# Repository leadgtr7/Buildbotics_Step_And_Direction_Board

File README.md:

Buildbotics Step and Direction Breakout and Level Shifter
======

### Intro
This is a step and direction breakout board and level shifter for the awesome Buildbotics CNC controller (https://buildbotics.com/ and https://github.com/buildbotics).

This board has been tested with the CL57Y closed loop stepper driver (https://www.omc-stepperonline.com/closed-loop-stepper-driver/y-series-closed-loop-stepper-driver-0-7-0a-24-50vdc-for-nema-17-23-24-stepper-motor.html).

I suspect that it will work with most drivers that have a minimum pulse width of 2.5uS even though the buildbotics control has a pulse width of 2 uS it just seems to work.

This board involves some small surface mount components (SOIC-8) so soldering skills are a must!

### You will need the following parts for the board

| Qty	| P/N	| Digikey Link |
| ---- | ---- | ---- | 
|4x	|SN75451BDR	|https://www.digikey.com/product-detail/en/texas-instruments/SN75451BDR/296-14960-1-ND/562591|
|12x	|Generic Header Pins 2.54mm spacing	|https://www.amazon.com/MCIGICM-Header-2-45mm-Arduino-Connector/dp/B07PKKY8BX/ref=sr_1_4?keywords=header+pins&qid=1579894443&sr=8-4|
|2x	|PCB-MB-01|https://www.digikey.com/product-detail/en/essentra-components/PCB-MB-01/RPC1760-ND/393158|
|4x |3 pin plugable terminal blocks 3.81mm spacing |https://www.amazon.com/gp/product/B07SVNGBZ7/ref=ppx_yo_dt_b_search_asin_title?ie=UTF8&psc=1|
|4x |0805 0.1uF Cap|https://www.digikey.com/product-detail/en/stackpole-electronics-inc/CML0805Y5V104ZT50V/738-CML0805Y5V104ZT50VCT-ND/10660252|

### Buildbotics PCB Modifications
You will need to solder in headers to the bbctrl board to make step and direction available as well as a 2 pin header with 5v and Ground. This will vary based on the version of your control board. You can find the schematics for the differnt revs here (https://github.com/buildbotics/bbctrl-pcb/tree/master/doc). For my controller (rev 8) you can see below for the locations.

You will also need to make a harness to connect the 10 pins on the bbctrl to the step and direction board. If you aren't comfortable crimping your own harness you could use something like this (https://www.amazon.com/EDGELEC-Breadboard-Optional-Assorted-Multicolored/dp/B07GCY6CH7/ref=sr_1_3?keywords=header%2Bwire&qid=1579895256&sr=8-3&th=1) for your harness.

### PCB Assembly
The image below shows the location of all the headers and how to solder the ICs to the board. Each of the 3 pin connectors provides the step and direction output and the 4 sets of 2 pins are wired to the buildbotics pcb header you need to install. Remeber that as you plug in the cable on the back that they will be reversed on the front so pay attention to that.

note the direction of pin 1 of the IC's

### New Back Panel
The back of the buildbotics controller can be modified to accommodate the new board using the any of the files in the back panel folder. I use fusion 360 so i have included a fusion file with all of my tool paths and the like. You could also use the step file. 

I Used 1/16th in aluminum sheet to recreate the back piece (https://www.amazon.com/dp/B00HRHBB20/?coliid=IMIUESINE7ACL&colid=2XXWKYU69Q3UG&psc=1&ref_=lv_ov_lig_dp_it).

back panel

I think that about covers it. Thanks to Joe and Doug from buildbotics for an awesome product and helping me out in modifying the controller to suit my needs.

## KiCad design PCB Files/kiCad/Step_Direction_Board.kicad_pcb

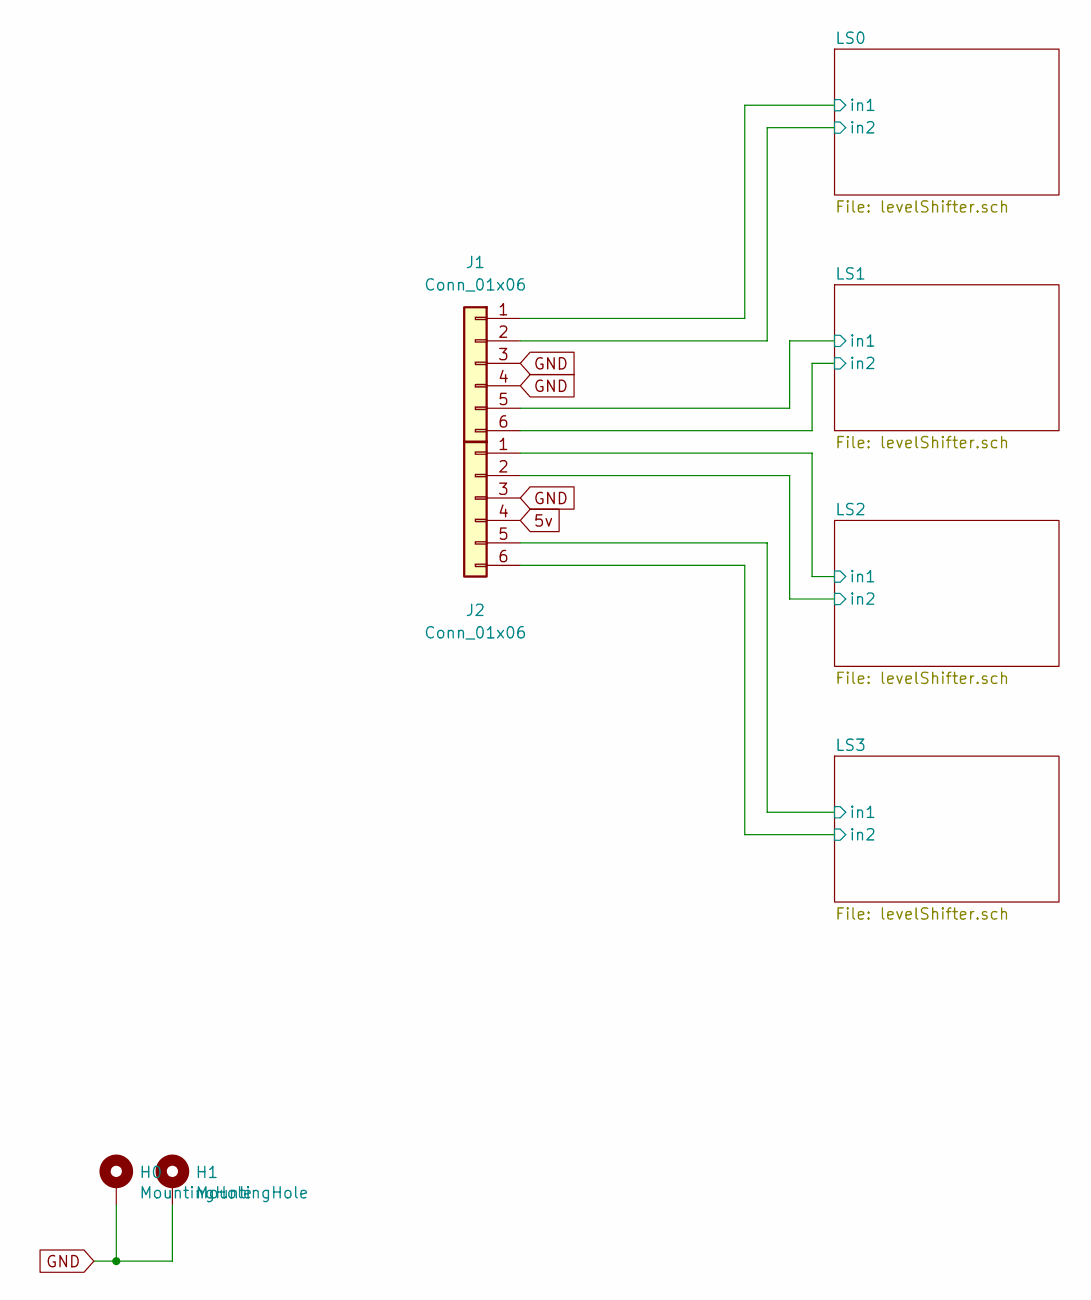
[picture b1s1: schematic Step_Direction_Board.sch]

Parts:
H0, H1: MountingHole; MountingHole_3.2mm_M3_ISO7380_Pad
J1, J2: Conn_01x06; PinHeader_1x06_P2.54mm_Horizontal

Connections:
5v: J2.4; also elsewhere on the board
/LS0/in1: J1.1; also elsewhere on the board
/LS0/in2: J1.2; also elsewhere on the board
/LS1/in1: J1.5; also elsewhere on the board
/LS1/in2: J1.6; also elsewhere on the board
/LS2/in1: J2.1; also elsewhere on the board
/LS2/in2: J2.2; also elsewhere on the board
/LS3/in1: J2.5; also elsewhere on the board
/LS3/in2: J2.6; also elsewhere on the board
GND: H0.1, H1.1, J1.3, J1.4, J2.3; also elsewhere on the board

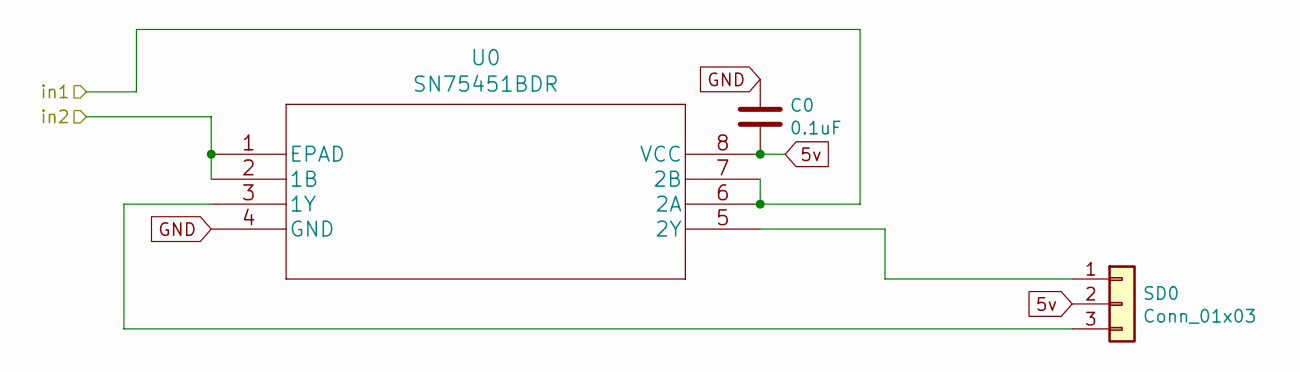
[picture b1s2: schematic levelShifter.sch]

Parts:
C0: 0.1uF; C_0805_2012Metric_Pad1.15x1.40mm_HandSolder
SD0: Conn_01x03; PhoenixContact_MC_1,5_3-G-3.81_1x03_P3.81mm_Horizontal
U0: SN75451BDR

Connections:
5v: C0.2, SD0.2, U0.8 (VCC); also elsewhere on the board
/LS0/in1: U0.6 (2A), U0.7 (2B); also elsewhere on the board
/LS0/in2: U0.1 (EPAD), U0.2 (1B); also elsewhere on the board
GND: C0.1, U0.4 (GND); also elsewhere on the board
unnamed: SD0.1, U0.5 (2Y)
unnamed: SD0.3, U0.3 (1Y)

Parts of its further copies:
C1, C2, C3: 0.1uF; C_0805_2012Metric_Pad1.15x1.40mm_HandSolder
SD1, SD2, SD3: Conn_01x03; PhoenixContact_MC_1,5_3-G-3.81_1x03_P3.81mm_Horizontal
U1, U2, U3: SN75451BDR

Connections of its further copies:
5v: C1.2, C2.2, C3.2, SD1.2, SD2.2, SD3.2, U1.8 (VCC), U2.8 (VCC), U3.8 (VCC); also elsewhere on the board
/LS1/in1: U1.6 (2A), U1.7 (2B); also elsewhere on the board
/LS1/in2: U1.1 (EPAD), U1.2 (1B); also elsewhere on the board
/LS2/in1: U2.6 (2A), U2.7 (2B); also elsewhere on the board
/LS2/in2: U2.1 (EPAD), U2.2 (1B); also elsewhere on the board
/LS3/in1: U3.6 (2A), U3.7 (2B); also elsewhere on the board
/LS3/in2: U3.1 (EPAD), U3.2 (1B); also elsewhere on the board
GND: C1.1, C2.1, C3.1, U1.4 (GND), U2.4 (GND), U3.4 (GND); also elsewhere on the board
unnamed: SD1.1, U1.5 (2Y)
unnamed: SD1.3, U1.3 (1Y)
unnamed: SD2.1, U2.5 (2Y)
unnamed: SD2.3, U2.3 (1Y)
unnamed: SD3.1, U3.5 (2Y)
unnamed: SD3.3, U3.3 (1Y)

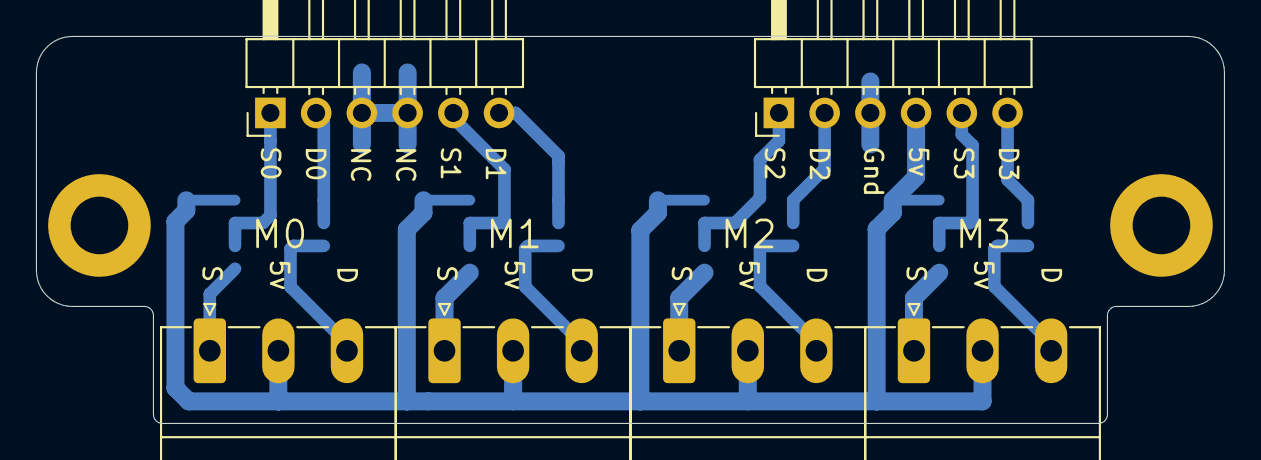
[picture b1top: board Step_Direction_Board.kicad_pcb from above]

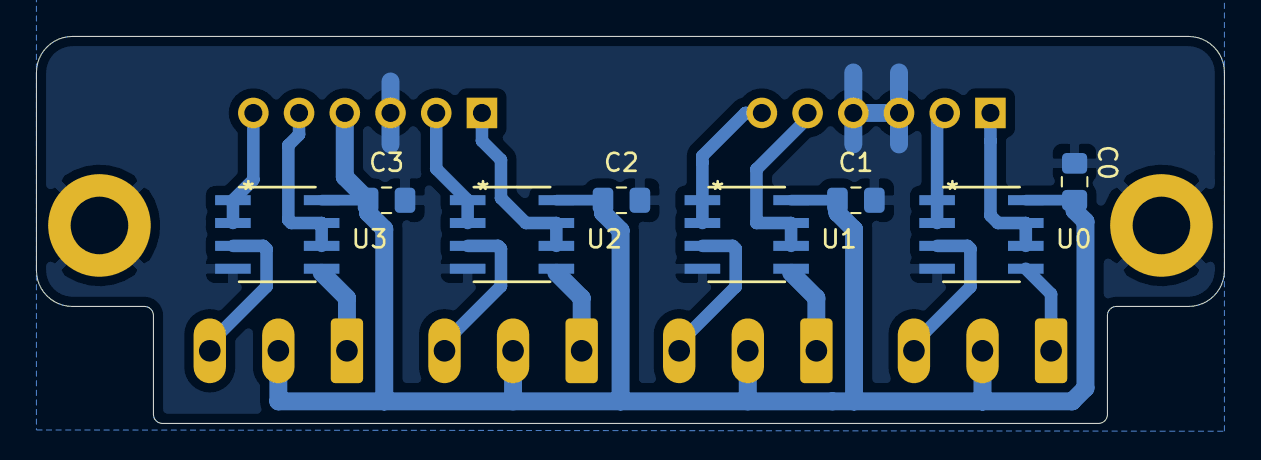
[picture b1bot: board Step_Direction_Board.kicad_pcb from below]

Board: 2 copper layers, 66.0 x 21.5 mm, 16 parts (8 on the bottom side), 18 nets.

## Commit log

2020-06-05 New And Updated Files
2020-06-05 let's try this again

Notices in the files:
parts and their libraries:
Copyright 2016 Accelerated Designs. All rights reserved.
